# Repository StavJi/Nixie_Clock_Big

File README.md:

# NixieClockBig
Nixie clock with ZM1080 tubes

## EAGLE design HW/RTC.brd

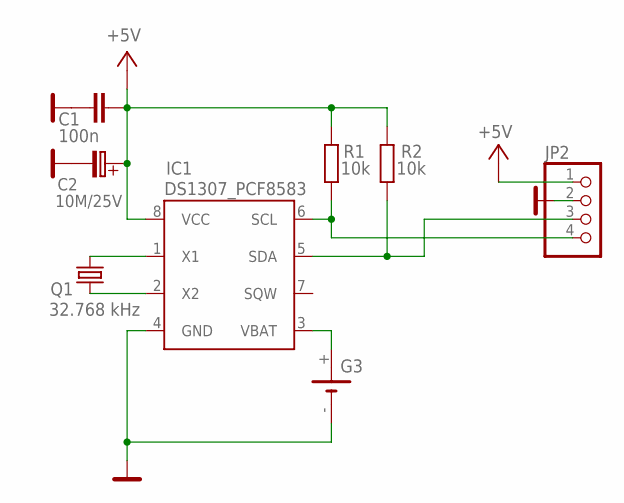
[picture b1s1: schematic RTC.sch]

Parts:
C1: 100n; KERAMICKY_RM5
C2: 10M/25V; C_EL_2
G3: VL1220
IC1: DS1307_PCF8583; DS1307_PCF8583_DIL08
JP2: PINHD-1X4; 1X04
Q1: 32.768 kHz; GWX-26
R1, R2: 10k; 0207/10

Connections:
+5V: C1.P$1 (1), C2.C+ (C_EL+), IC1.8 (VCC), JP2.1, R1.2, R2.2
GND: C1.P$2 (2), C2.C- (C_EL-), G3.-, IC1.4 (GND), JP2.2
unnamed: IC1.6 (SCL), JP2.4, R1.1
unnamed: IC1.5 (SDA), JP2.3, R2.1
unnamed: IC1.1 (X1), Q1.P$2 (2)
unnamed: IC1.2 (X2), Q1.P$1 (1)
unnamed: G3.+, IC1.3 (VBAT)

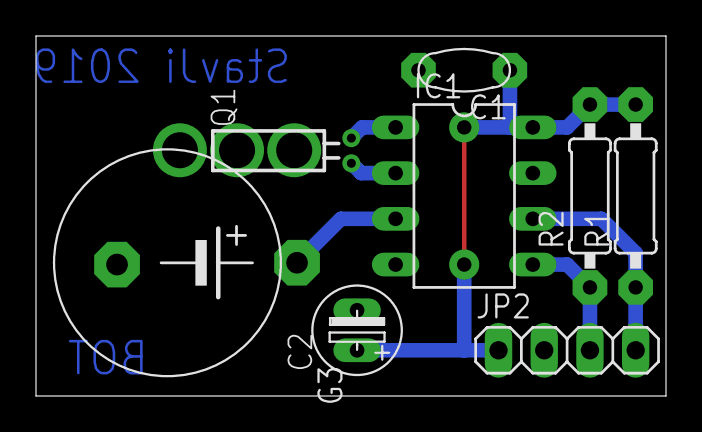
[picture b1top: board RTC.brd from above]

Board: 2 copper layers, 35.0 x 20.0 mm, 8 parts (0 on the bottom side), 7 nets.

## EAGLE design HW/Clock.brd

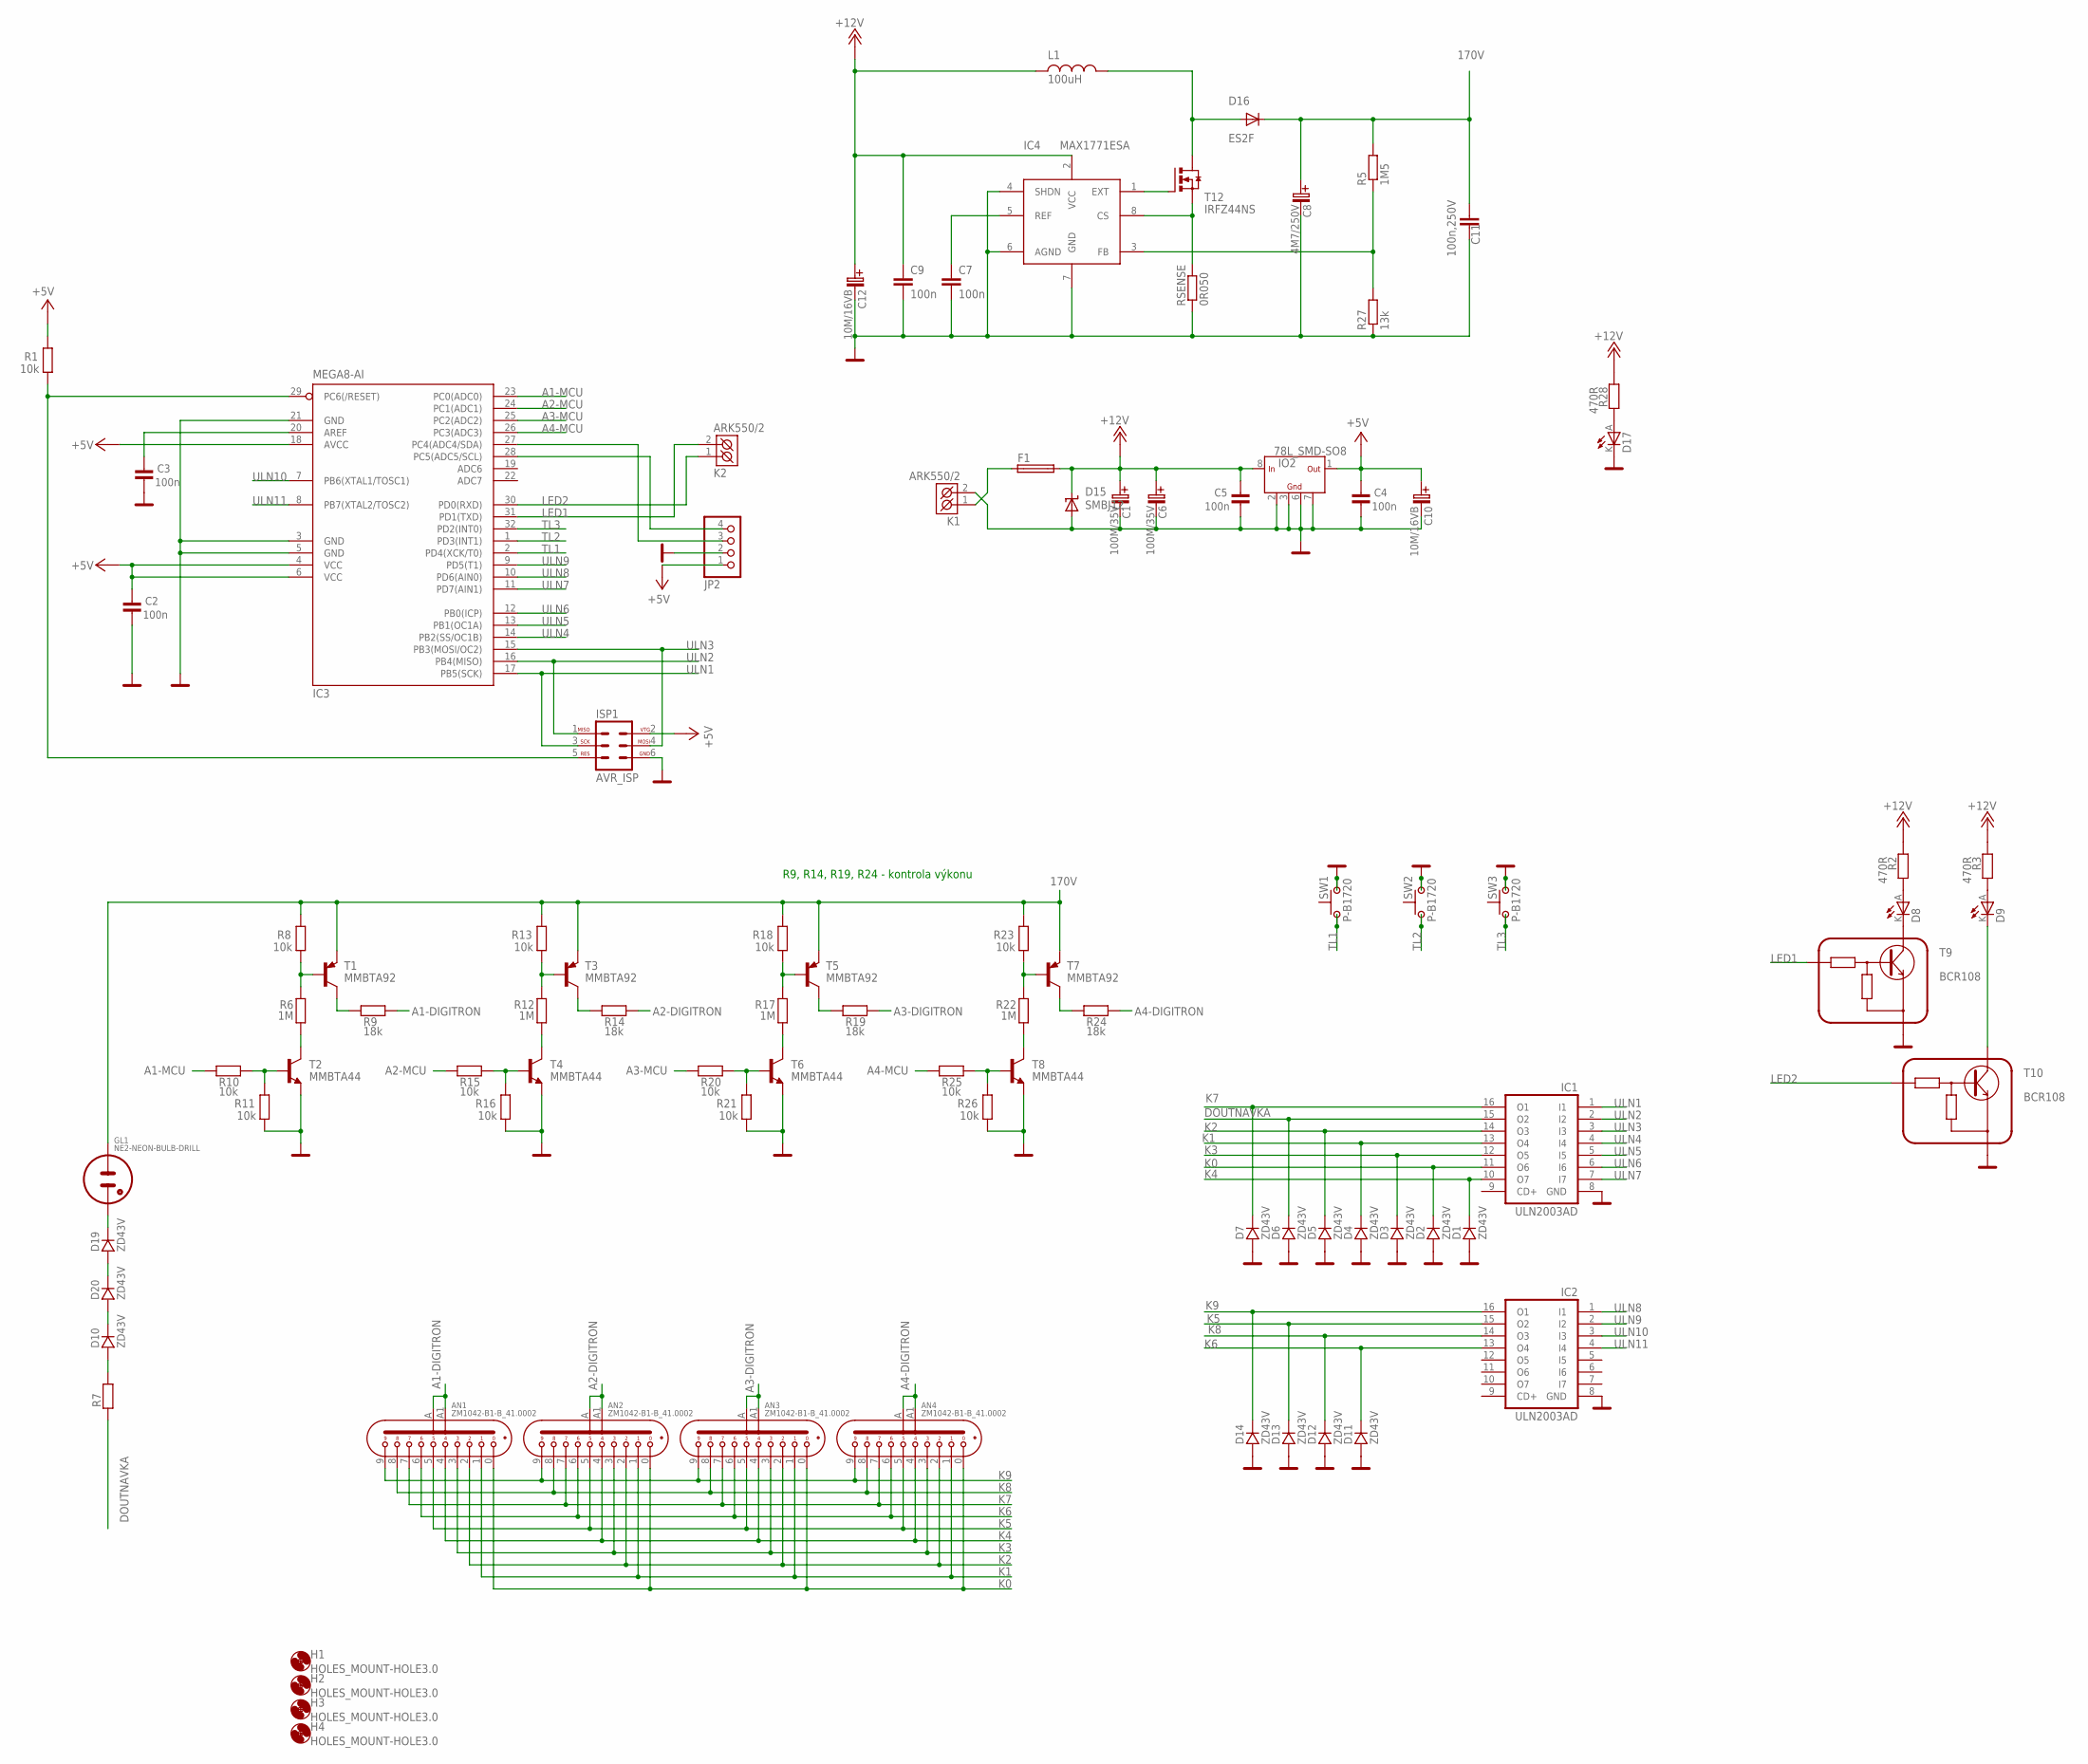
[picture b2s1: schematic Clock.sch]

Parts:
AN1, AN2, AN3, AN4: ZM1042-B1-B_41.0002; ZM1042-MULTI-CONTACT
C1, C6: 100M/35V; C_EL_3,5
C2, C3, C4, C5: 100n; 0805
C7, C9: 100n; C0805
C8: 4M7/250V; C_EL_3,5
C10, C12: 10M/16VB; B
C11: 100n,250V; C2420
D1, D2, D3, D4, D5, D6, D7, D10, D11, D12, D13, D14, D19, D20: ZD43V; SOD-80
D8, D9, D17: LEDLED3MM; LED3MM
D15: SMBJ12; SMBJ
D16: ES2F; SMC
F1: TE5
GL1: NE2-NEON-BULB-DRILL
H1, H2, H3, H4: HOLES_MOUNT-HOLE3.0; HOLES_3,0
IC1, IC2: ULN2003AD; SO16
IC3: MEGA8-AI; TQFP32-08
IC4: MAX1771ESA; SO-8
IO2: 78L_SMD-SO8; SO08
ISP1: AVR_ISP; MLW06G
JP2: PINHD-1X4; 1X04
K1, K2: ARK550/2
L1: 100uH; L-B82479
R1, R8, R10, R11, R13, R15, R16, R18, R20, R21, R23, R25, R26: 10k; 0805
R2, R3, R28: 470R; 0805
R5: 1M5; R0805
R6, R12, R17, R22: 1M; 0805
R7: W2_180K; R__2W
R9, R14, R19, R24: 18k; 1206
R27: 13k; R0805
RSENSE: 0R050; R2010
SW1, SW2, SW3: P-B1720
T1, T3, T5, T7: MMBTA92; SOT23-BEC
T2, T4, T6, T8: MMBTA44; SOT23-BEC
T9, T10: BCR108; SOT-23
T12: IRFZ44NS; D2PACK

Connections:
170V: C8.C+ (C_EL+), C11.P$1 (1), D16.C, GL1.1 (A), R5.2, R8.2, R13.2, R18.2, R23.2, T1.E, T3.E, T5.E, T7.E
+5V: C2.2, C4.2, C10.+ (C_EL+), IC3.4 (VCC), IC3.6 (VCC), IC3.18 (AVCC), IO2.1 (OUT), ISP1.2, JP2.1, R1.2
A1-DIGITRON: AN1.A (A1), AN1.A1 (A2), R9.1
A1-MCU: IC3.23 (PC0(ADC0)), R10.2
A2-DIGITRON: AN2.A (A1), AN2.A1 (A2), R14.1
A2-MCU: IC3.24 (PC1(ADC1)), R15.2
A3-DIGITRON: AN3.A (A1), AN3.A1 (A2), R19.1
A3-MCU: IC3.25 (PC2(ADC2)), R20.2
A4-DIGITRON: AN4.A (A1), AN4.A1 (A2), R24.1
A4-MCU: IC3.26 (PC3(ADC3)), R25.2
DCF: IC3.27 (PC4(ADC4/SDA)), JP2.3
DOUTNAVKA: D6.K, IC1.15 (O2), R7.1
EXT: IC4.1 (EXT), T12.1 (G)
GND: C1.C- (C_EL-), C2.1, C3.1, C4.1, C5.1, C6.C- (C_EL-), C7.2, C8.C- (C_EL-), C9.2, C10.- (C_EL-), C11.P$2 (2), C12.- (C_EL-), D1.A, D2.A, D3.A, D4.A, D5.A, D6.A, D7.A, D11.A, D12.A, D13.A, D14.A, D15.A, D17.K (C), IC1.8 (GND), IC2.8 (GND), IC3.3 (GND), IC3.5 (GND), IC3.21 (GND), IC4.4 (SHDN), IC4.6 (AGND), IC4.7 (GND), IO2.2 (GND), IO2.3 (GND), IO2.6 (GND), IO2.7 (GND), ISP1.6, JP2.2, K1.2 (K2), R11.1, R16.1, R21.1, R26.1, R27.1, RSENSE.1, SW1.2, SW1.4, SW2.2, SW2.4, SW3.2, SW3.4, T2.E, T4.E, T6.E, T8.E, T9.2 (E), T10.2 (E)
K0: AN1.0, AN2.0, AN3.0, AN4.0, D2.K, IC1.11 (O6)
K1: AN1.1, AN2.1, AN3.1, AN4.1, D4.K, IC1.13 (O4)
K2: AN1.2, AN2.2, AN3.2, AN4.2, D5.K, IC1.14 (O3)
K3: AN1.3, AN2.3, AN3.3, AN4.3, D3.K, IC1.12 (O5)
K4: AN1.4, AN2.4, AN3.4, AN4.4, D1.K, IC1.10 (O7)
K5: AN1.5, AN2.5, AN3.5, AN4.5, D13.K, IC2.15 (O2)
K6: AN1.6, AN2.6, AN3.6, AN4.6, D11.K, IC2.13 (O4)
K7: AN1.7, AN2.7, AN3.7, AN4.7, D7.K, IC1.16 (O1)
K8: AN1.8, AN2.8, AN3.8, AN4.8, D12.K, IC2.14 (O3)
K9: AN1.9, AN2.9, AN3.9, AN4.9, D14.K, IC2.16 (O1)
LED1: IC3.31 (PD1(TXD)), K2.2 (K2), T9.1 (B)
LED2: IC3.30 (PD0(RXD)), K2.1 (K1), T10.1 (B)
LED3: IC3.28 (PC5(ADC5/SCL)), JP2.4
unnamed: C3.2, IC3.20 (AREF)
unnamed: C1.C+ (C_EL+), C5.2, C6.C+ (C_EL+), C9.1, C12.+ (C_EL+), D15.C, F1.2, IC4.2 (VCC), IO2.8 (IN), L1.P$1 (1), R2.2, R3.2, R28.2
unnamed: F1.1, K1.1 (K1)
unnamed: D8.K (C), T9.3 (C)
unnamed: D9.K (C), T10.3 (C)
unnamed: D10.A, R7.2
unnamed: D8.A, R2.1
unnamed: D9.A, R3.1
unnamed: D10.K, D20.A
unnamed: D19.K, GL1.2 (A1)
unnamed: IC4.3 (FB), R5.1, R27.2
unnamed: C7.1, IC4.5 (REF)
unnamed: D16.A, L1.P$2 (2), T12.2 (D)
unnamed: IC4.8 (CS), RSENSE.2, T12.3 (S)
unnamed: IC3.29 (PC6(/RESET)), ISP1.5, R1.1
unnamed: D19.A, D20.K
unnamed: D17.A, R28.1
unnamed: R6.2, R8.1, T1.B
unnamed: R9.2, T1.C
unnamed: R6.1, T2.C
unnamed: R10.1, R11.2, T2.B
unnamed: R12.2, R13.1, T3.B
unnamed: R14.2, T3.C
unnamed: R12.1, T4.C
unnamed: R15.1, R16.2, T4.B
unnamed: R17.2, R18.1, T5.B
unnamed: R19.2, T5.C
unnamed: R17.1, T6.C
unnamed: R20.1, R21.2, T6.B
unnamed: R22.2, R23.1, T7.B
unnamed: R24.2, T7.C
unnamed: R22.1, T8.C
unnamed: R25.1, R26.2, T8.B
TL1: IC3.2 (PD4(XCK/T0)), SW1.1, SW1.3
TL2: IC3.1 (PD3(INT1)), SW2.1, SW2.3
TL3: IC3.32 (PD2(INT0)), SW3.1, SW3.3
ULN1: IC1.1 (I1), IC3.17 (PB5(SCK)), ISP1.3
ULN2: IC1.2 (I2), IC3.16 (PB4(MISO)), ISP1.1
ULN3: IC1.3 (I3), IC3.15 (PB3(MOSI/OC2)), ISP1.4
ULN4: IC1.4 (I4), IC3.14 (PB2(SS/OC1B))
ULN5: IC1.5 (I5), IC3.13 (PB1(OC1A))
ULN6: IC1.6 (I6), IC3.12 (PB0(ICP))
ULN7: IC1.7 (I7), IC3.11 (PD7(AIN1))
ULN8: IC2.1 (I1), IC3.10 (PD6(AIN0))
ULN9: IC2.2 (I2), IC3.9 (PD5(T1))
ULN10: IC2.3 (I3), IC3.7 (PB6(XTAL1/TOSC1))
ULN11: IC2.4 (I4), IC3.8 (PB7(XTAL2/TOSC2))

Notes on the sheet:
R9, R14, R19, R24 - kontrola výkonu

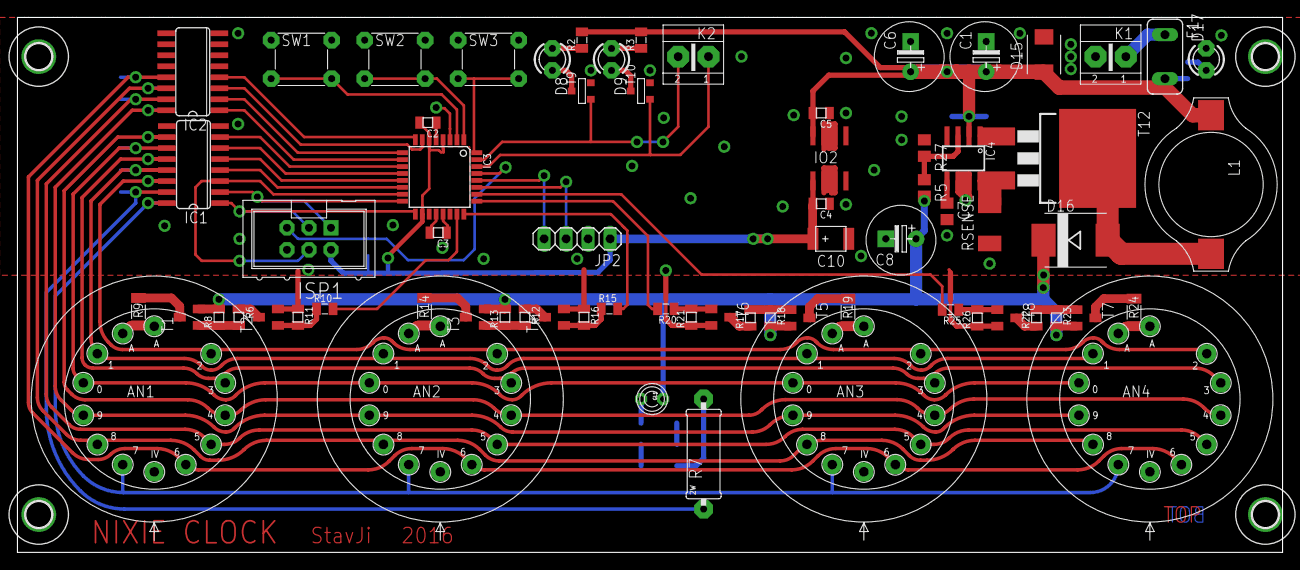
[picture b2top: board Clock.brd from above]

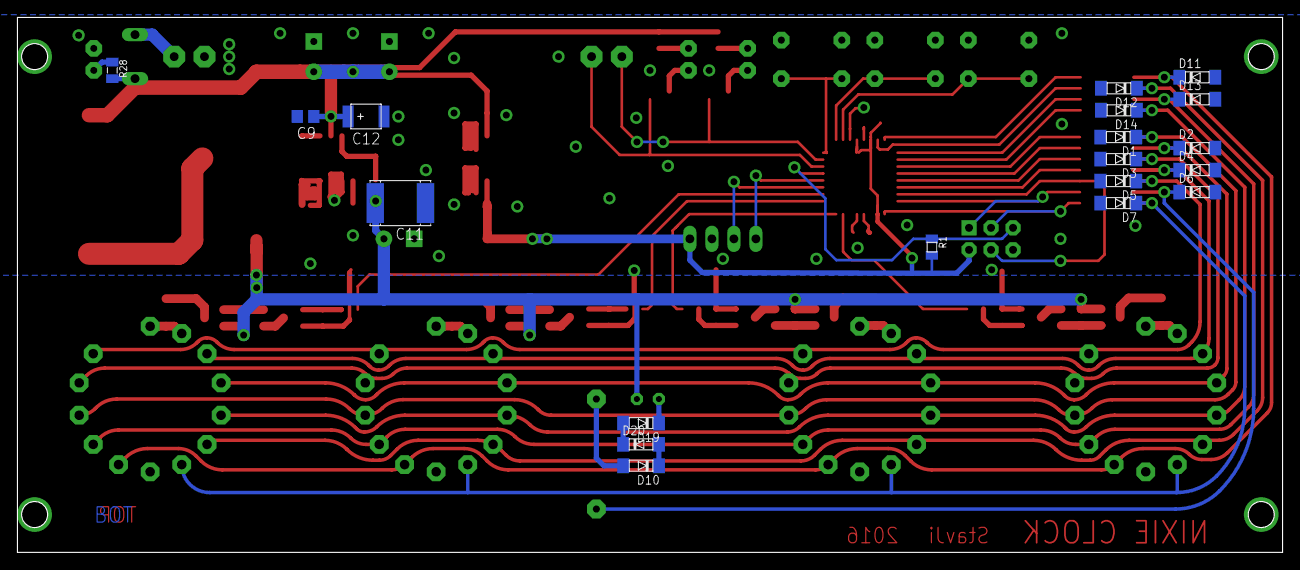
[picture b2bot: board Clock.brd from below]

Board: 2 copper layers, 146.1 x 61.8 mm, 93 parts (19 on the bottom side), 74 nets.

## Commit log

2019-08-15 draft of project
2021-03-16 feat: add AT cmd interface
2021-03-16 add design files
2021-03-16 add photo of finished clock
2021-03-16 add FW

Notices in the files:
parts and their libraries:
Copyright (C) PaJa 2001-2010
Copyright (C) PaJa 2001-2011
Copyright (C) PaJa 2011
Copyright (C) Vlada 2004-2005
Copyright (C) PaJa 2003-2009
Copyright (C) PaJa 2009
golledge_full_v1-0: © Golledge Electronics Ltd 2015. Released under GNU General Public License. Full library V1.0.
